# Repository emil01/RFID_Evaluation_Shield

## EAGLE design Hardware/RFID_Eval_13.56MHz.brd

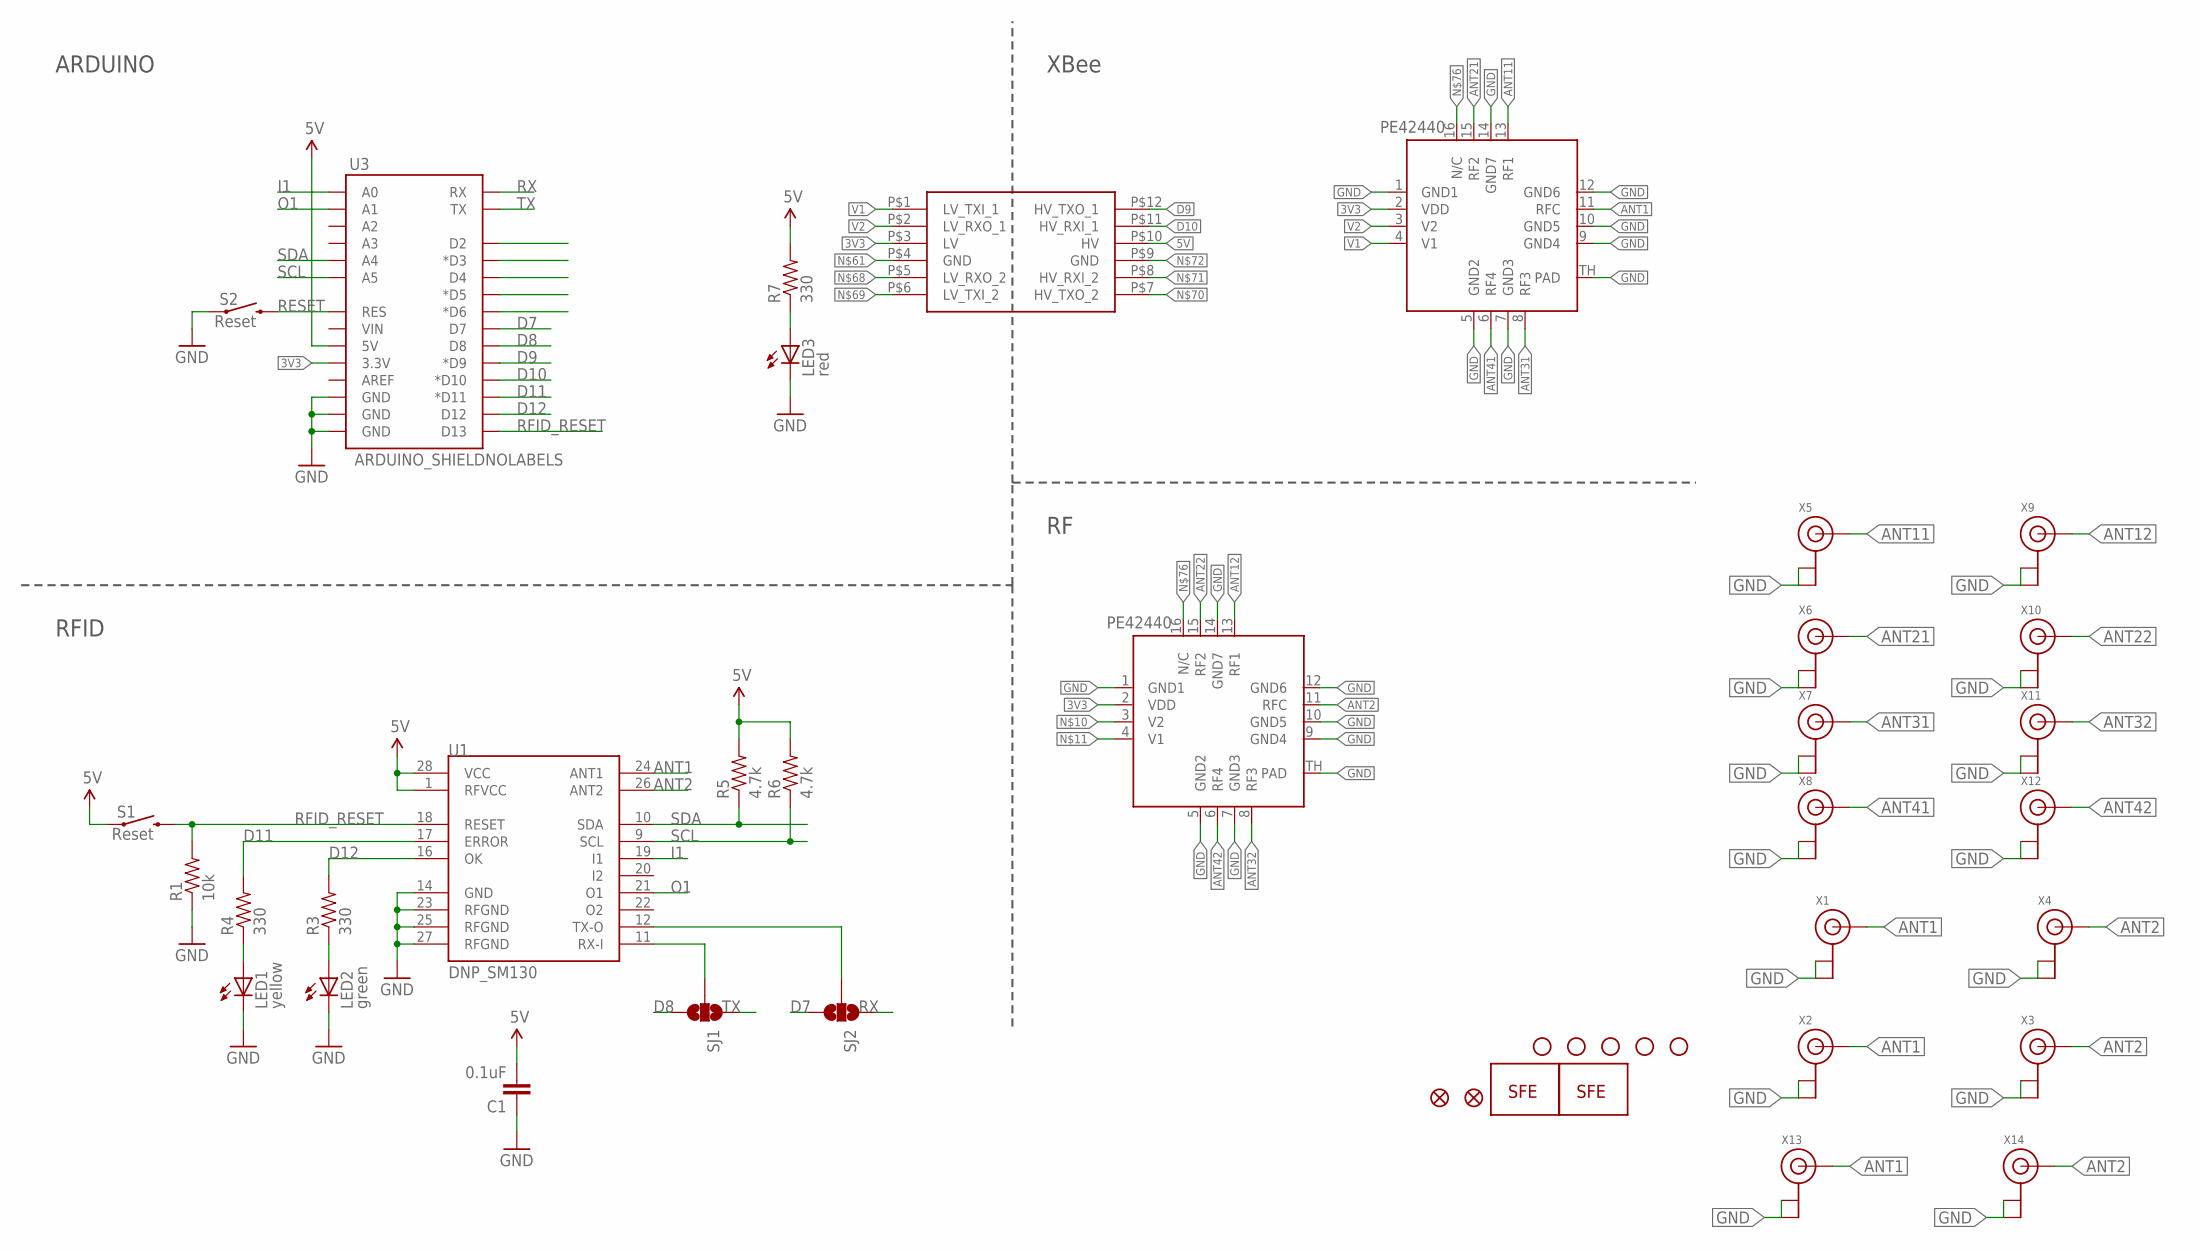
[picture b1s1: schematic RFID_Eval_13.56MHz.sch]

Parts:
C1: 0.1uF; 0402-CAP
JP2: LOGO-SFENEW; SFE-NEW-WEBLOGO
JP3, JP5, JP7, JP10, JP13: STAND-OFF
JP4: LOGO-SFESK; SFE-LOGO-FLAME
JP11, JP12: FIDUCIAL1X2; FIDUCIAL-1X2
LED1: yellow; LED-0603
LED2: green; LED-0603
LED3: red; LED-0603
R1: 10k; 0402-RES
R3, R4, R7: 330; 0402-RES
R5, R6: 4.7k; 0402-RES
S1, S2: Reset; TACTILE_SWITCH_SMD
SJ1, SJ2: SOLDERJUMPER_2WAYPASTE2&3; SJ_3_PASTE2&3
U1: DNP_SM130; SM130
U3: ARDUINO_SHIELDNOLABELS; DUEMILANOVE_SHIELD_NOLABELS
U$2: LOGIC_LEVEL_CONVERTER
U$8, U$9: PE42440; PQFP-N16
X1, X2, X3, X4, X5, X6, X7, X8, X9, X10, X11, X12, X13, X14: ANTENNA_U.FL; U.FL

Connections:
3V3: U3.3.3V, U$2.P$3 (LV), U$8.2 (VDD), U$9.2 (VDD)
5V: C1.2, R5.2, R6.2, R7.2, S1.1, U1.1 (RFVCC), U1.28 (VCC), U3.5V, U$2.P$10 (HV)
ANT1: U1.24 (ANT1), U$9.11 (RFC), X1.3 (SIGNAL), X2.3 (SIGNAL), X13.3 (SIGNAL)
ANT2: U1.26 (ANT2), U$8.11 (RFC), X3.3 (SIGNAL), X4.3 (SIGNAL), X14.3 (SIGNAL)
ANT11: U$9.13 (RF1), X5.3 (SIGNAL)
ANT12: U$8.13 (RF1), X9.3 (SIGNAL)
ANT21: U$9.15 (RF2), X6.3 (SIGNAL)
ANT22: U$8.15 (RF2), X10.3 (SIGNAL)
ANT31: U$9.8 (RF3), X7.3 (SIGNAL)
ANT32: U$8.8 (RF3), X11.3 (SIGNAL)
ANT41: U$9.6 (RF4), X8.3 (SIGNAL)
ANT42: U$8.6 (RF4), X12.3 (SIGNAL)
D7: SJ2.3, U3.D7
D8: SJ1.3, U3.D8
D9: U3.D9 (*D9), U$2.P$12 (HV_TXO_1)
D10: U3.D10 (*D10), U$2.P$11 (HV_RXI_1)
D11: R4.2, U1.17 (ERROR), U3.D11 (*D11)
D12: R3.2, U1.16 (OK), U3.D12
GND: C1.1, LED1.C, LED2.C, LED3.C, R1.1, S2.1, U1.14 (GND), U1.23 (RFGND), U1.25 (RFGND), U1.27 (RFGND), U3.GND@0 (GND), U3.GND@1 (GND), U3.GND@2 (GND), U$8.1 (GND1), U$8.5 (GND2), U$8.7 (GND3), U$8.9 (GND4), U$8.10 (GND5), U$8.12 (GND6), U$8.14 (GND7), U$8.TH (PAD), U$9.1 (GND1), U$9.5 (GND2), U$9.7 (GND3), U$9.9 (GND4), U$9.10 (GND5), U$9.12 (GND6), U$9.14 (GND7), U$9.TH (PAD), X1.1 (GND), X1.2 (GND), X2.1 (GND), X2.2 (GND), X3.1 (GND), X3.2 (GND), X4.1 (GND), X4.2 (GND), X5.1 (GND), X5.2 (GND), X6.1 (GND), X6.2 (GND), X7.1 (GND), X7.2 (GND), X8.1 (GND), X8.2 (GND), X9.1 (GND), X9.2 (GND), X10.1 (GND), X10.2 (GND), X11.1 (GND), X11.2 (GND), X12.1 (GND), X12.2 (GND), X13.1 (GND), X13.2 (GND), X14.1 (GND), X14.2 (GND)
I1: U1.19 (I1), U3.A0
unnamed: LED1.A, R4.1
unnamed: LED2.A, R3.1
unnamed: LED3.A, R7.1
unnamed: SJ2.2, U1.12 (TX-O)
unnamed: SJ1.2, U1.11 (RX-I)
unnamed: U$8.16 (N/C), U$9.16 (N/C)
O1: U1.21 (O1), U3.A1
RESET: S2.3 (2), U3.RES
RFID_RESET: R1.2, S1.3 (2), U1.18 (RESET), U3.D13
RX: SJ2.1, U3.RX
SCL: R6.1, U1.9 (SCL), U3.A5
SDA: R5.1, U1.10 (SDA), U3.A4
TX: SJ1.1, U3.TX
V1: U$2.P$1 (LV_TXI_1), U$9.4 (V1)
V2: U$2.P$2 (LV_RXO_1), U$9.3 (V2)

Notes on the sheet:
ARDUINO
XBee
RFID

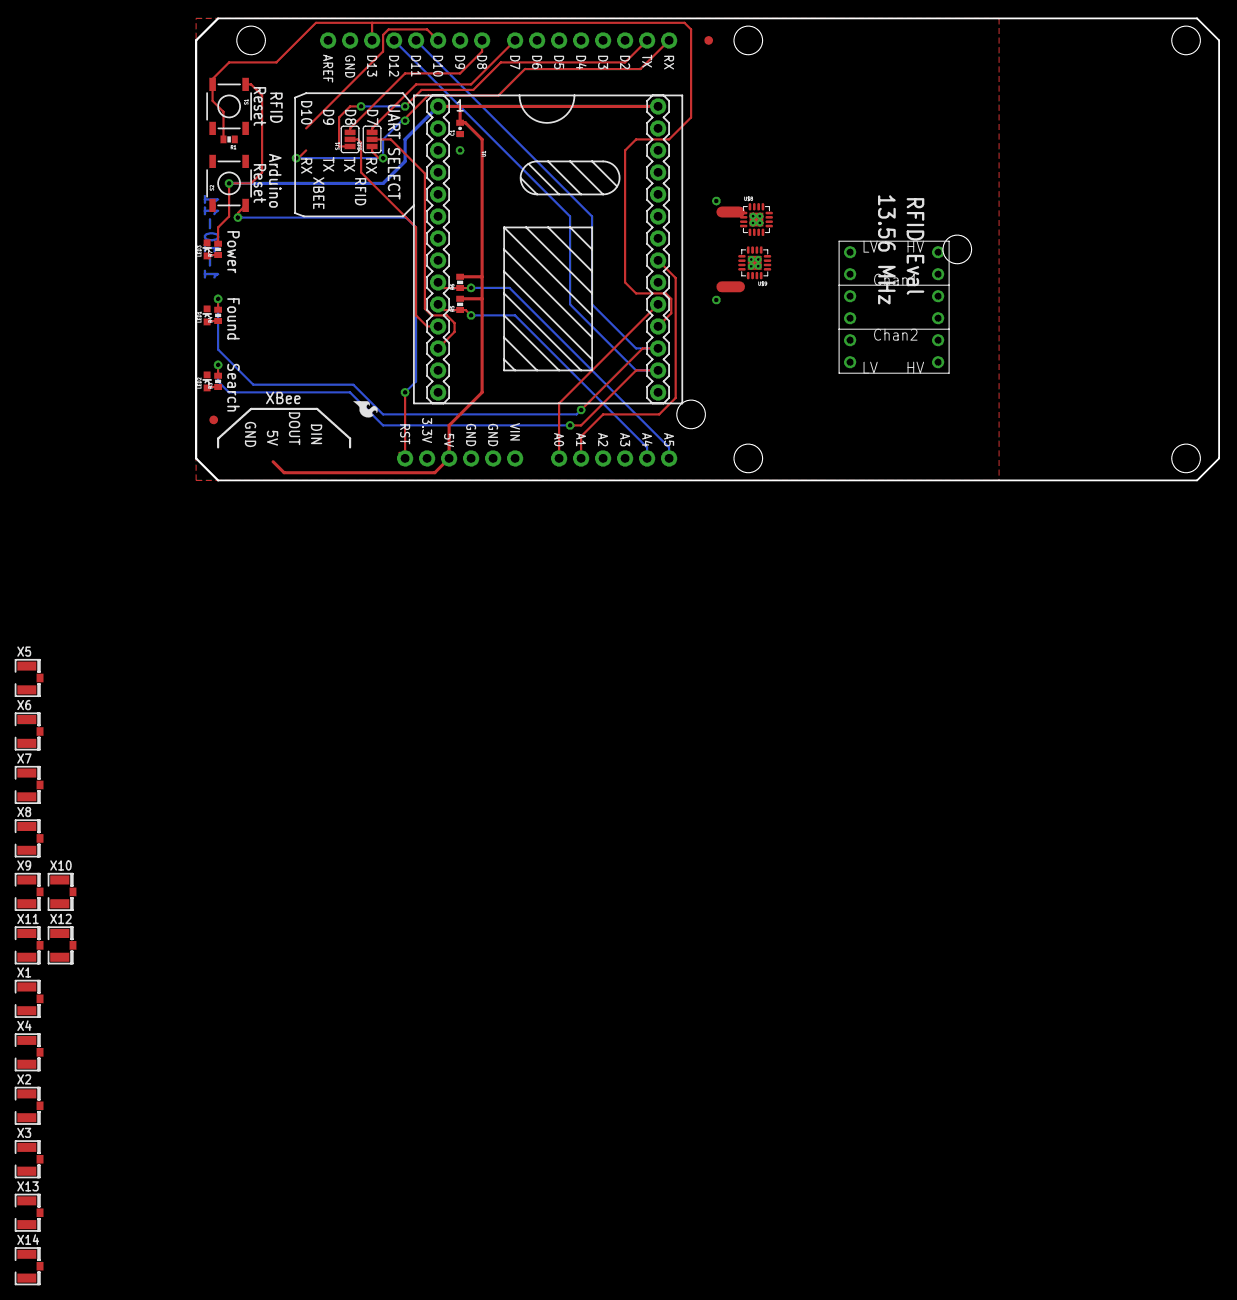
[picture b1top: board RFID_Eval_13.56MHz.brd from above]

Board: 2 copper layers, 118.1 x 53.3 mm, 42 parts (1 on the bottom side), 35 nets.

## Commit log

2016-02-16 Done: Removed all other components other than the antenna
    To be Done:
    Need to add the antenna connector and RF Switch etc.
2016-02-17 Think I completed the antenna design
2016-02-17 Need to check schematics
2016-02-17 Added 3 more u.FL connectors for testing purpose

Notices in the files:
parts and their libraries:
SparkFun-Boards: Licensing: Creative Commons ShareAlike 4.0 International - https://creativecommons.org/licenses/by-sa/4.0
